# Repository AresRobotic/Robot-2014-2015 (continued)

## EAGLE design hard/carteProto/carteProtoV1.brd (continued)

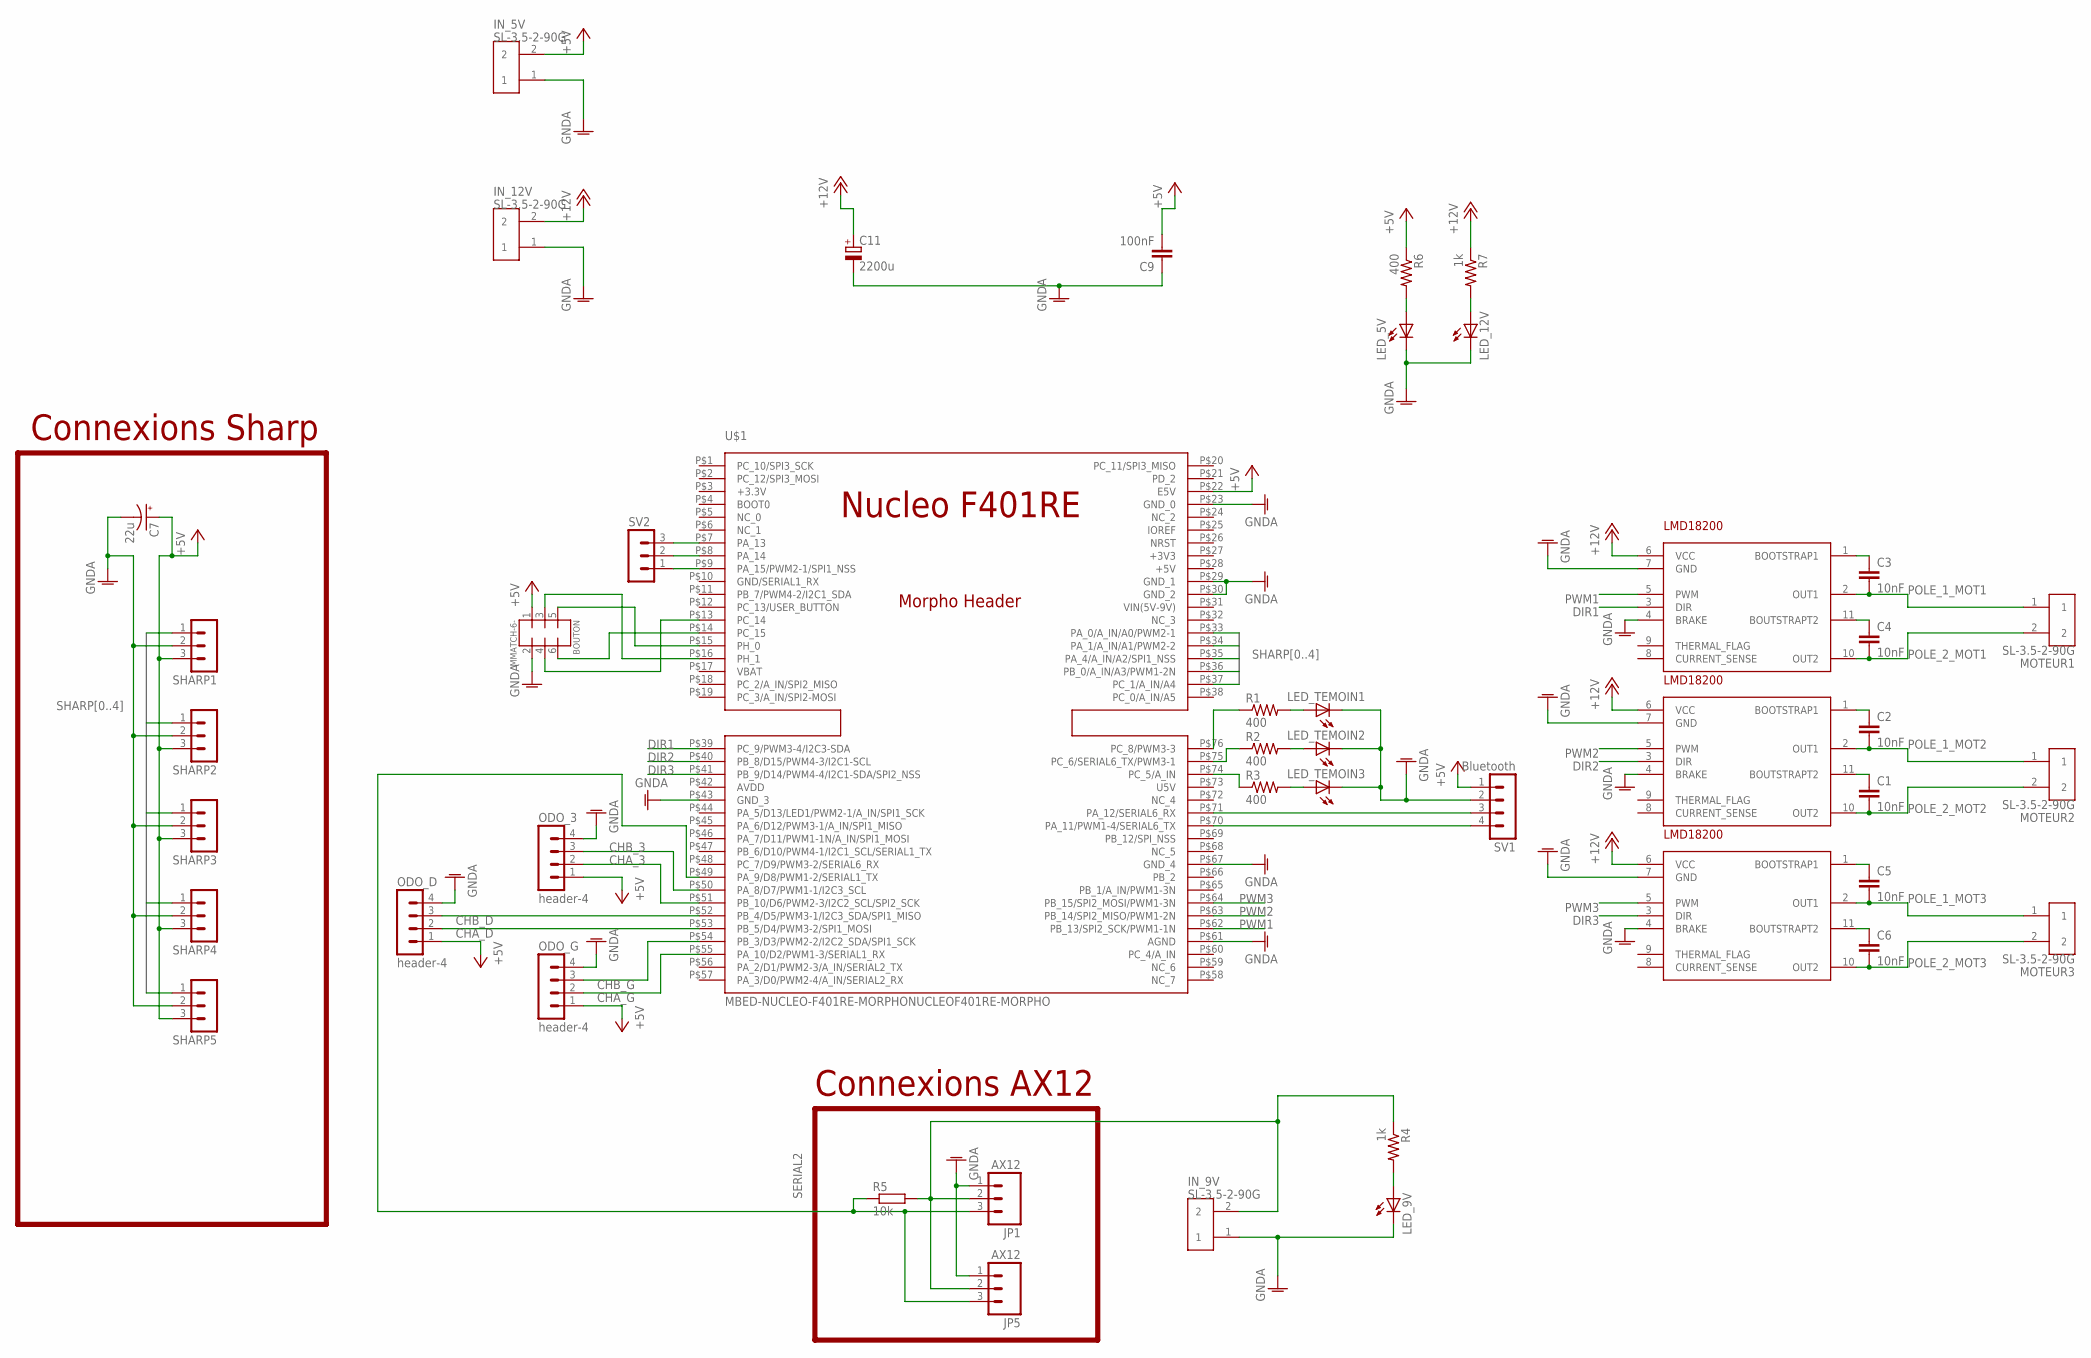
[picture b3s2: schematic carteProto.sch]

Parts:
BOUTON: MMATCH-6-; AMP-215079-6
C1, C2, C3, C4, C5, C6: 10nF; C0805
C7: 22u; CPOL-RADIAL-100UF-25V
C9: 100nF; C0805
C11: 2200u; TT5D11
IN_5V, IN_9V, IN_12V: SL-3.5-2-90G
JP1, JP5: AX12; MOLEX-1X3
LED_5V, LED_9V, LED_12V: LEDCHIPLED_0805; CHIPLED_0805
LED_TEMOIN1, LED_TEMOIN2, LED_TEMOIN3: LEDCHIPLED_0805; CHIPLED_0805
MOTEUR1, MOTEUR2, MOTEUR3: SL-3.5-2-90G
ODO_3: header-4; MA04-1
ODO_D: header-4; MA04-1
ODO_G: header-4; MA04-1
R1, R2, R3, R6: 400; 0805
R4, R7: 1k; 0805
R5: 10k; M0805
SHARP1, SHARP2, SHARP3, SHARP4, SHARP5: MA03-1
SV1: Bluetooth; MA04-1
SV2: MA03-1
U$1: MBED-NUCLEO-F401RE-MORPHONUCLEOF401RE-MORPHO; MORPHO-HEADERS
U$2, U$3, U$4: LMD18200

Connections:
+5V: BOUTON.1 (3), C7.1 (+), C9.2, IN_5V.2, ODO_3.1, ODO_D.1, ODO_G.1, R6.1, SHARP1.3, SHARP2.3, SHARP3.3, SHARP4.3, SHARP5.3, SV1.1, U$1.P$22 (E5V); also elsewhere on the board
CHA_3: ODO_3.2, U$1.P$51 (PB_10/D6/PWM2-3/I2C2_SCL/SPI2_SCK)
CHA_D: ODO_D.2, U$1.P$53 (PB_5/D4/PWM3-2/SPI1_MOSI)
CHA_G: ODO_G.2, U$1.P$55 (PA_10/D2/PWM1-3/SERIAL1_RX)
CHB_3: ODO_3.3, U$1.P$50 (PA_8/D7/PWM1-1/I2C3_SCL)
CHB_D: ODO_D.3, U$1.P$52 (PB_4/D5/PWM3-1/I2C3_SDA/SPI1_MISO)
CHB_G: ODO_G.3, U$1.P$54 (PB_3/D3/PWM2-2/I2C2_SDA/SPI1_SCK)
DIR1: U$1.P$39 (PC_9/PWM3-4/I2C3-SDA), U$2.3 (DIR)
DIR2: U$1.P$40 (PB_8/D15/PWM4-3/I2C1-SCL), U$3.3 (DIR)
DIR3: U$1.P$41 (PB_9/D14/PWM4-4/I2C1-SDA/SPI2_NSS), U$4.3 (DIR)
GNDA: BOUTON.2 (4), C7.2 (-), C9.1, C11.-, IN_5V.1, IN_9V.1, IN_12V.1, JP1.1, JP5.1, LED_5V.C, LED_9V.C, LED_12V.C, LED_TEMOIN1.C, LED_TEMOIN2.C, LED_TEMOIN3.C, ODO_3.4, ODO_D.4, ODO_G.4, SHARP1.2, SHARP2.2, SHARP3.2, SHARP4.2, SHARP5.2, SV1.2, U$1.P$23 (GND_0), U$1.P$29 (GND_1), U$1.P$30 (GND_2), U$1.P$43 (GND_3), U$1.P$61 (AGND), U$1.P$67 (GND_4), U$2.4 (BRAKE), U$2.7 (GND), U$3.4 (BRAKE), U$3.7 (GND), U$4.4 (BRAKE), U$4.7 (GND); also elsewhere on the board
unnamed: C1.1, U$3.11 (BOUTSTRAPT2)
unnamed: C5.1, U$4.1 (BOOTSTRAP1)
unnamed: C2.1, U$3.1 (BOOTSTRAP1)
unnamed: C6.1, U$4.11 (BOUTSTRAPT2)
unnamed: C3.1, U$2.1 (BOOTSTRAP1)
unnamed: SV1.3, U$1.P$71 (PA_12/SERIAL6_RX)
unnamed: C4.1, U$2.11 (BOUTSTRAPT2)
unnamed: SV1.4, U$1.P$70 (PA_11/PWM1-4/SERIAL6_TX)
unnamed: LED_5V.A, R6.2
unnamed: LED_TEMOIN3.A, R3.2
unnamed: LED_12V.A, R7.2
unnamed: R1.1, U$1.P$76 (PC_8/PWM3-3)
unnamed: R2.1, U$1.P$75 (PC_6/SERIAL6_TX/PWM3-1)
unnamed: R3.1, U$1.P$74 (PC_5/A_IN)
unnamed: LED_TEMOIN1.A, R1.2
unnamed: LED_TEMOIN2.A, R2.2
unnamed: BOUTON.3 (5), U$1.P$16 (PH_1)
unnamed: BOUTON.5 (7), U$1.P$15 (PH_0)
unnamed: BOUTON.6 (8), U$1.P$14 (PC_15)
unnamed: BOUTON.4 (6), U$1.P$13 (PC_14)
unnamed: SV2.3, U$1.P$7 (PA_13)
unnamed: SV2.2, U$1.P$8 (PA_14)
unnamed: SV2.1, U$1.P$9 (PA_15/PWM2-1/SPI1_NSS)
unnamed: LED_9V.A, R4.2
POLE_1_MOT1: C3.2, MOTEUR1.1, U$2.2 (OUT1)
POLE_1_MOT2: C2.2, MOTEUR2.1, U$3.2 (OUT1)
POLE_1_MOT3: C5.2, MOTEUR3.1, U$4.2 (OUT1)
POLE_2_MOT1: C4.2, MOTEUR1.2, U$2.10 (OUT2)
POLE_2_MOT2: C1.2, MOTEUR2.2, U$3.10 (OUT2)
POLE_2_MOT3: C6.2, MOTEUR3.2, U$4.10 (OUT2)
PWM1: U$1.P$62 (PB_13/SPI2_SCK/PWM1-1N), U$2.5 (PWM)
PWM2: U$1.P$63 (PB_14/SPI2_MISO/PWM1-2N), U$3.5 (PWM)
PWM3: U$1.P$64 (PB_15/SPI2_MOSI/PWM1-3N), U$4.5 (PWM)
SERIAL2: JP1.3, JP5.3, R5.1, U$1.P$49 (PA_9/D8/PWM1-2/SERIAL1_TX); also elsewhere on the board
SHARP0: SHARP1.1, U$1.P$33 (PA_0/A_IN/A0/PWM2-1)
SHARP1: SHARP2.1, U$1.P$34 (PA_1/A_IN/A1/PWM2-2)
SHARP2: SHARP3.1, U$1.P$35 (PA_4/A_IN/A2/SPI1_NSS)
SHARP3: SHARP4.1, U$1.P$36 (PB_0/A_IN/A3/PWM1-2N)
SHARP4: SHARP5.1, U$1.P$37 (PC_1/A_IN/A4)

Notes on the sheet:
Connexions Sharp
Connexions AX12

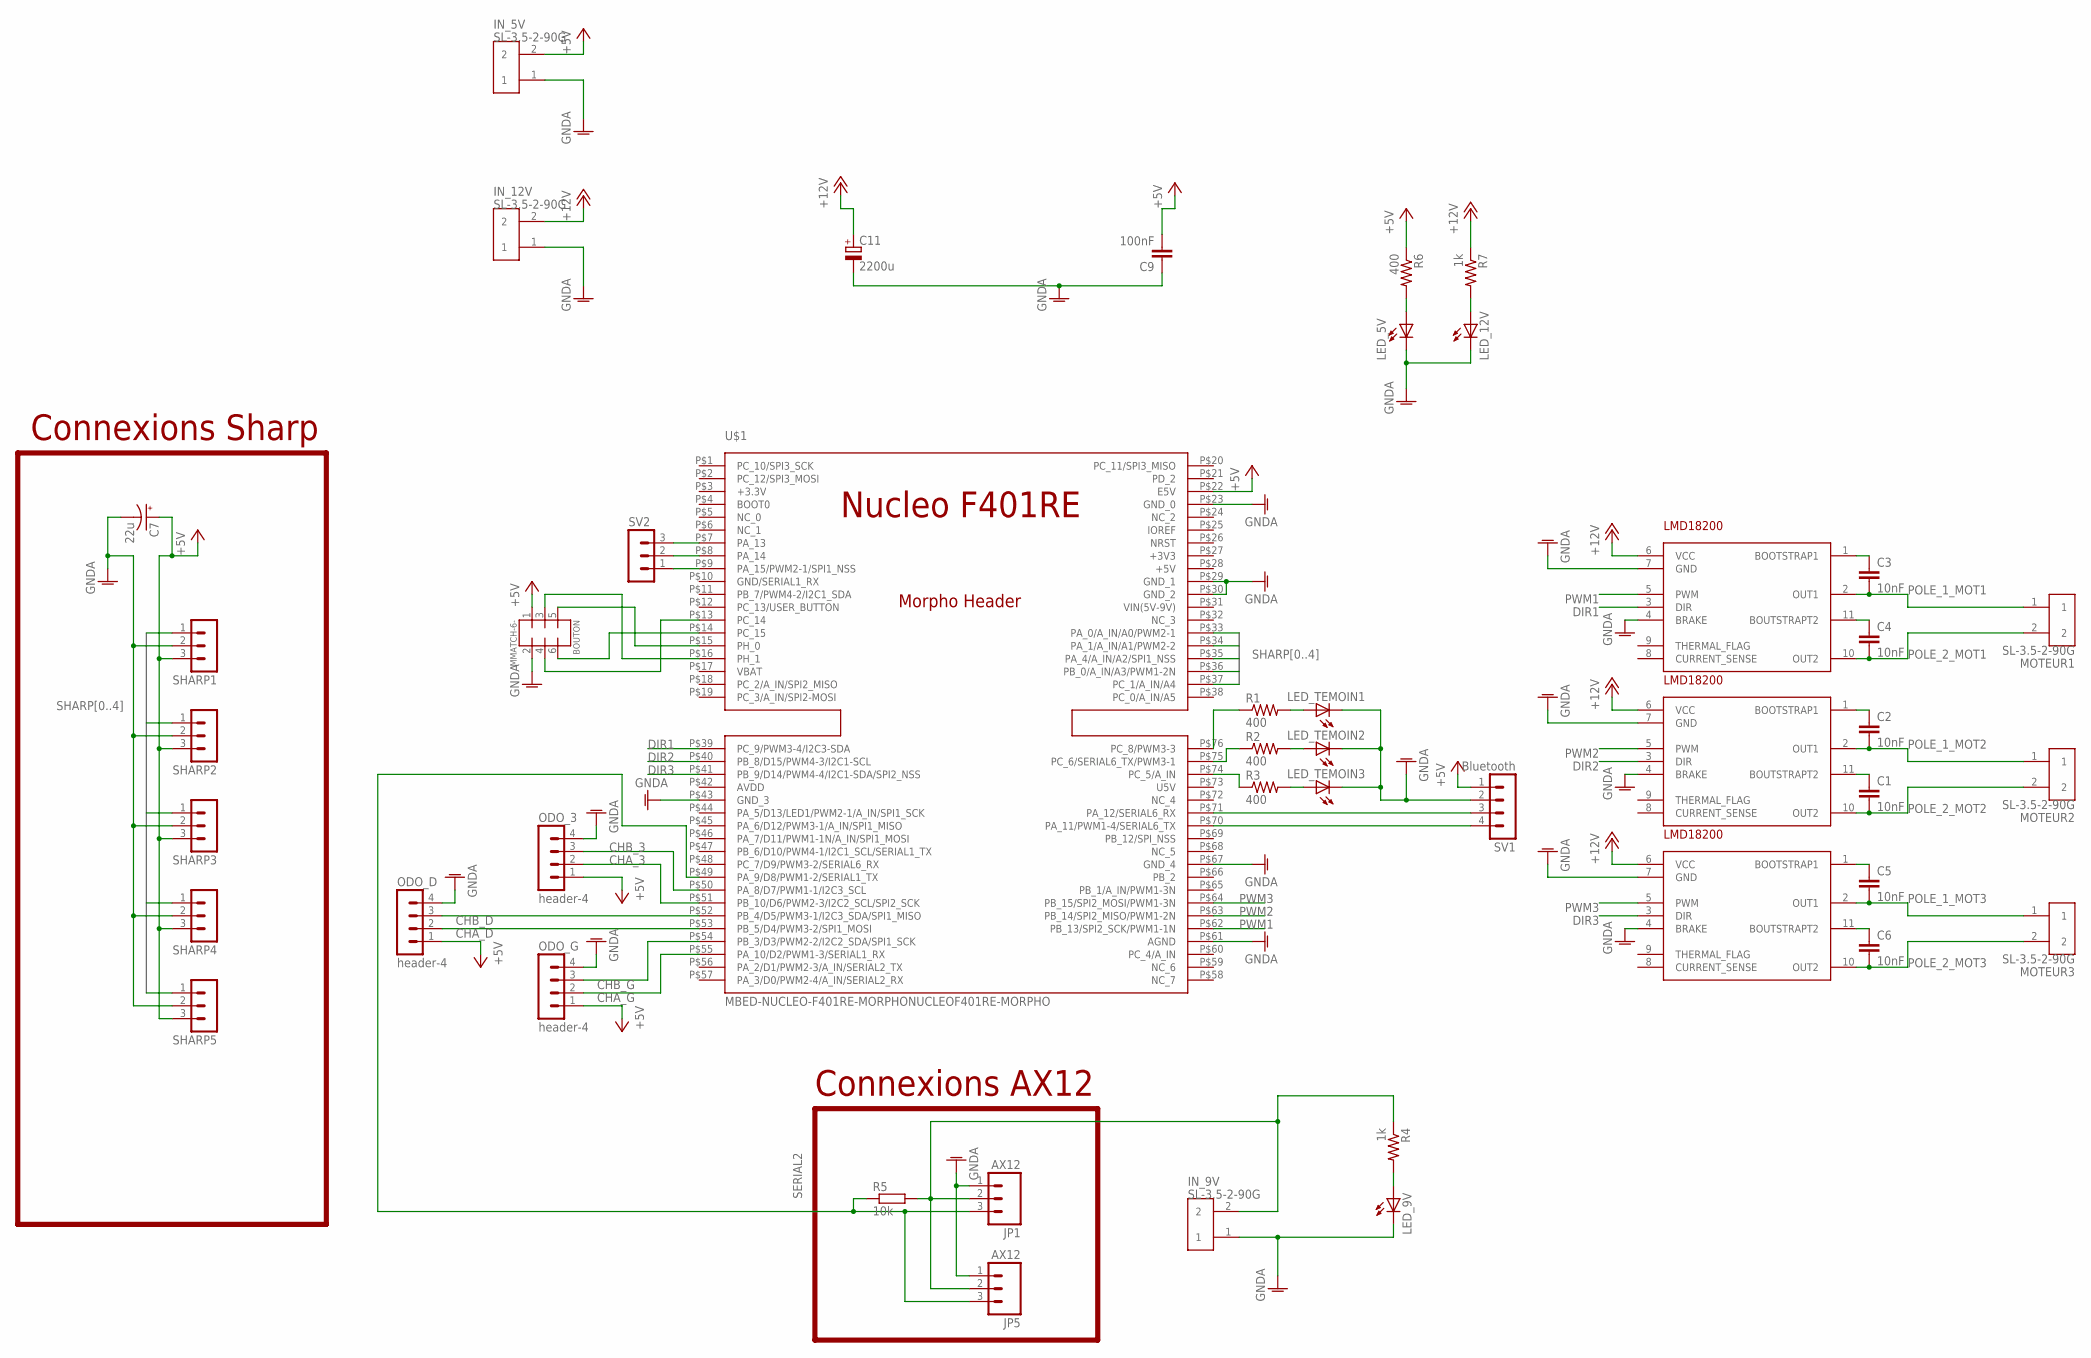
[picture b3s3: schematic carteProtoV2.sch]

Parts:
BOUTON: MMATCH-6-; AMP-215079-6
C1, C2, C3, C4, C5, C6: 10nF; C0805
C7: 22u; CPOL-RADIAL-100UF-25V
C9: 100nF; C0805
C11: 2200u; TT5D11
IN_5V, IN_9V, IN_12V: SL-3.5-2-90G
JP1, JP5: AX12; MOLEX-1X3
LED_5V, LED_9V, LED_12V: LEDCHIPLED_0805; CHIPLED_0805
LED_TEMOIN1, LED_TEMOIN2, LED_TEMOIN3: LEDCHIPLED_0805; CHIPLED_0805
MOTEUR1, MOTEUR2, MOTEUR3: SL-3.5-2-90G
ODO_3: header-4; MA04-1
ODO_D: header-4; MA04-1
ODO_G: header-4; MA04-1
R1, R2, R3, R6: 400; 0805
R4, R7: 1k; 0805
R5: 10k; M0805
SHARP1, SHARP2, SHARP3, SHARP4, SHARP5: MA03-1
SV1: Bluetooth; MA04-1
SV2: MA03-1
U$1: MBED-NUCLEO-F401RE-MORPHONUCLEOF401RE-MORPHO; MORPHO-HEADERS
U$2, U$3, U$4: LMD18200

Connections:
+5V: BOUTON.1 (3), C7.1 (+), C9.2, IN_5V.2, ODO_3.1, ODO_D.1, ODO_G.1, R6.1, SHARP1.3, SHARP2.3, SHARP3.3, SHARP4.3, SHARP5.3, SV1.1, U$1.P$22 (E5V); also elsewhere on the board
CHA_3: ODO_3.2, U$1.P$51 (PB_10/D6/PWM2-3/I2C2_SCL/SPI2_SCK)
CHA_D: ODO_D.2, U$1.P$53 (PB_5/D4/PWM3-2/SPI1_MOSI)
CHA_G: ODO_G.2, U$1.P$55 (PA_10/D2/PWM1-3/SERIAL1_RX)
CHB_3: ODO_3.3, U$1.P$50 (PA_8/D7/PWM1-1/I2C3_SCL)
CHB_D: ODO_D.3, U$1.P$52 (PB_4/D5/PWM3-1/I2C3_SDA/SPI1_MISO)
CHB_G: ODO_G.3, U$1.P$54 (PB_3/D3/PWM2-2/I2C2_SDA/SPI1_SCK)
DIR1: U$1.P$39 (PC_9/PWM3-4/I2C3-SDA), U$2.3 (DIR)
DIR2: U$1.P$40 (PB_8/D15/PWM4-3/I2C1-SCL), U$3.3 (DIR)
DIR3: U$1.P$41 (PB_9/D14/PWM4-4/I2C1-SDA/SPI2_NSS), U$4.3 (DIR)
GNDA: BOUTON.2 (4), C7.2 (-), C9.1, C11.-, IN_5V.1, IN_9V.1, IN_12V.1, JP1.1, JP5.1, LED_5V.C, LED_9V.C, LED_12V.C, LED_TEMOIN1.C, LED_TEMOIN2.C, LED_TEMOIN3.C, ODO_3.4, ODO_D.4, ODO_G.4, SHARP1.2, SHARP2.2, SHARP3.2, SHARP4.2, SHARP5.2, SV1.2, U$1.P$23 (GND_0), U$1.P$29 (GND_1), U$1.P$30 (GND_2), U$1.P$43 (GND_3), U$1.P$61 (AGND), U$1.P$67 (GND_4), U$2.4 (BRAKE), U$2.7 (GND), U$3.4 (BRAKE), U$3.7 (GND), U$4.4 (BRAKE), U$4.7 (GND); also elsewhere on the board
unnamed: C1.1, U$3.11 (BOUTSTRAPT2)
unnamed: C5.1, U$4.1 (BOOTSTRAP1)
unnamed: C2.1, U$3.1 (BOOTSTRAP1)
unnamed: C6.1, U$4.11 (BOUTSTRAPT2)
unnamed: C3.1, U$2.1 (BOOTSTRAP1)
unnamed: SV1.3, U$1.P$71 (PA_12/SERIAL6_RX)
unnamed: C4.1, U$2.11 (BOUTSTRAPT2)
unnamed: SV1.4, U$1.P$70 (PA_11/PWM1-4/SERIAL6_TX)
unnamed: LED_5V.A, R6.2
unnamed: LED_TEMOIN3.A, R3.2
unnamed: LED_12V.A, R7.2
unnamed: R1.1, U$1.P$76 (PC_8/PWM3-3)
unnamed: R2.1, U$1.P$75 (PC_6/SERIAL6_TX/PWM3-1)
unnamed: R3.1, U$1.P$74 (PC_5/A_IN)
unnamed: LED_TEMOIN1.A, R1.2
unnamed: LED_TEMOIN2.A, R2.2
unnamed: BOUTON.3 (5), U$1.P$16 (PH_1)
unnamed: BOUTON.5 (7), U$1.P$15 (PH_0)
unnamed: BOUTON.6 (8), U$1.P$14 (PC_15)
unnamed: BOUTON.4 (6), U$1.P$13 (PC_14)
unnamed: SV2.3, U$1.P$7 (PA_13)
unnamed: SV2.2, U$1.P$8 (PA_14)
unnamed: SV2.1, U$1.P$9 (PA_15/PWM2-1/SPI1_NSS)
unnamed: LED_9V.A, R4.2
POLE_1_MOT1: C3.2, MOTEUR1.1, U$2.2 (OUT1)
POLE_1_MOT2: C2.2, MOTEUR2.1, U$3.2 (OUT1)
POLE_1_MOT3: C5.2, MOTEUR3.1, U$4.2 (OUT1)
POLE_2_MOT1: C4.2, MOTEUR1.2, U$2.10 (OUT2)
POLE_2_MOT2: C1.2, MOTEUR2.2, U$3.10 (OUT2)
POLE_2_MOT3: C6.2, MOTEUR3.2, U$4.10 (OUT2)
PWM1: U$1.P$62 (PB_13/SPI2_SCK/PWM1-1N), U$2.5 (PWM)
PWM2: U$1.P$63 (PB_14/SPI2_MISO/PWM1-2N), U$3.5 (PWM)
PWM3: U$1.P$64 (PB_15/SPI2_MOSI/PWM1-3N), U$4.5 (PWM)
SERIAL2: JP1.3, JP5.3, R5.1, U$1.P$49 (PA_9/D8/PWM1-2/SERIAL1_TX); also elsewhere on the board
SHARP0: SHARP1.1, U$1.P$33 (PA_0/A_IN/A0/PWM2-1)
SHARP1: SHARP2.1, U$1.P$34 (PA_1/A_IN/A1/PWM2-2)
SHARP2: SHARP3.1, U$1.P$35 (PA_4/A_IN/A2/SPI1_NSS)
SHARP3: SHARP4.1, U$1.P$36 (PB_0/A_IN/A3/PWM1-2N)
SHARP4: SHARP5.1, U$1.P$37 (PC_1/A_IN/A4)

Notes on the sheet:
Connexions Sharp
Connexions AX12

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
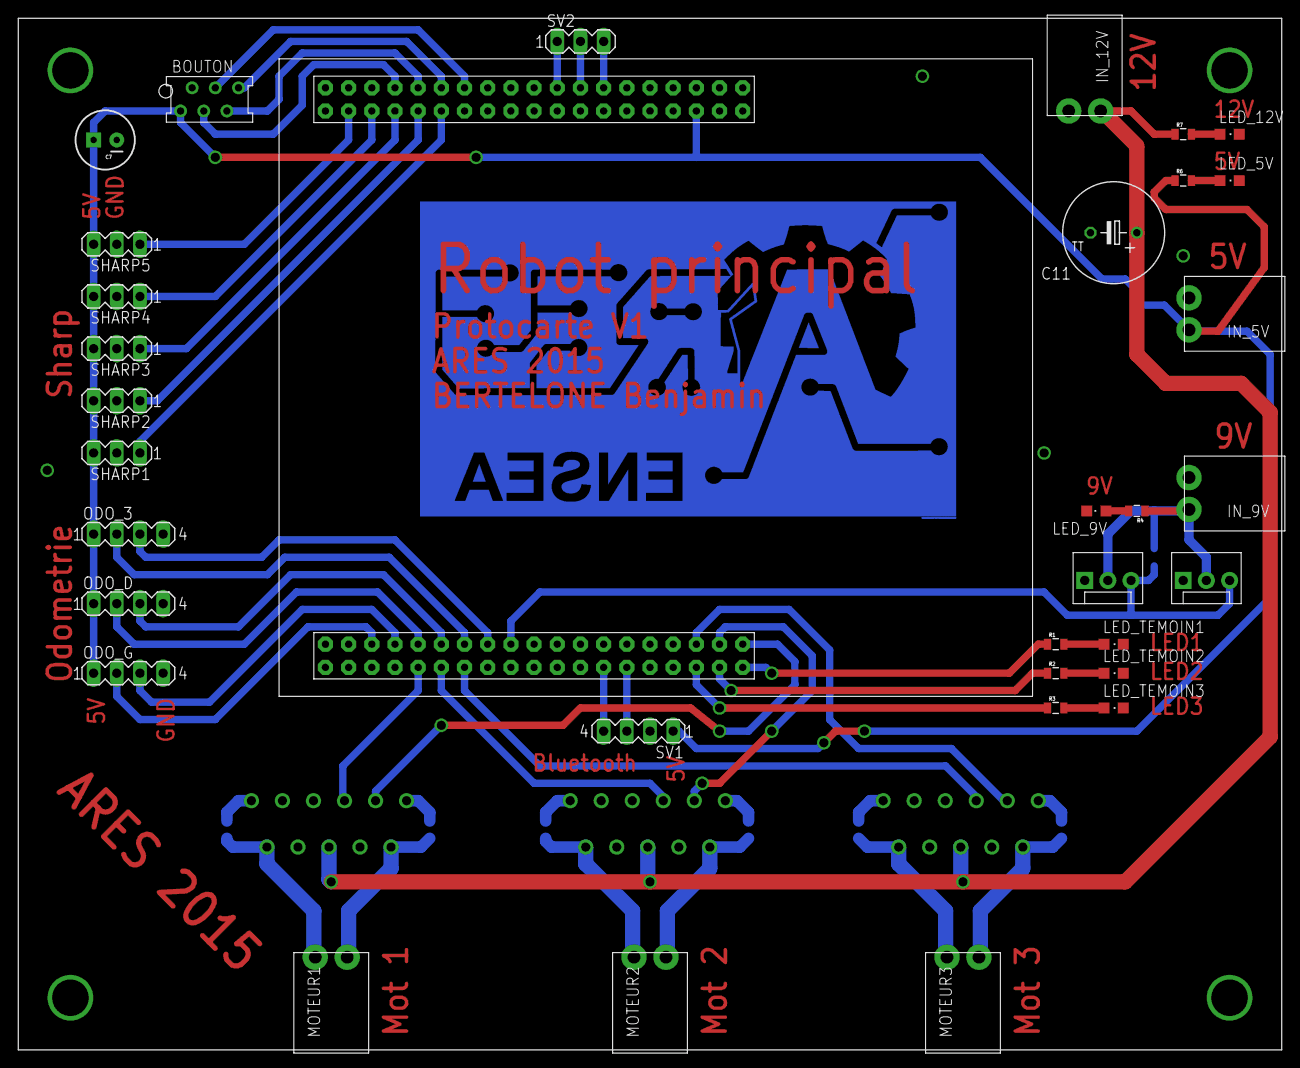
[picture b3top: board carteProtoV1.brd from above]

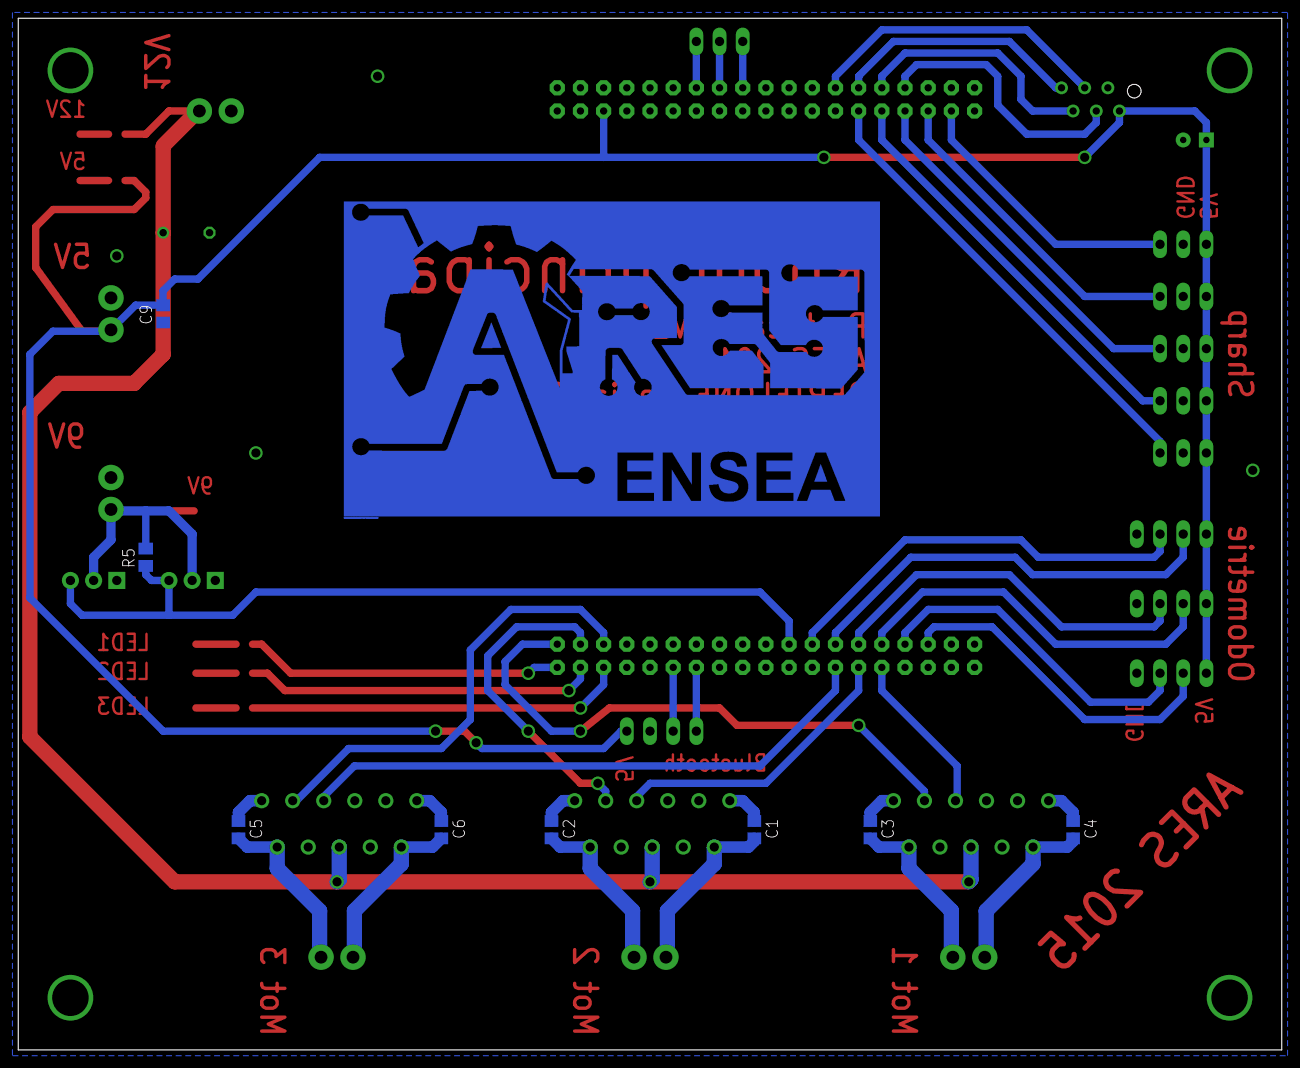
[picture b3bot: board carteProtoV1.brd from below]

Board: 2 copper layers, 138.4 x 113.0 mm, 45 parts (8 on the bottom side), 52 nets.

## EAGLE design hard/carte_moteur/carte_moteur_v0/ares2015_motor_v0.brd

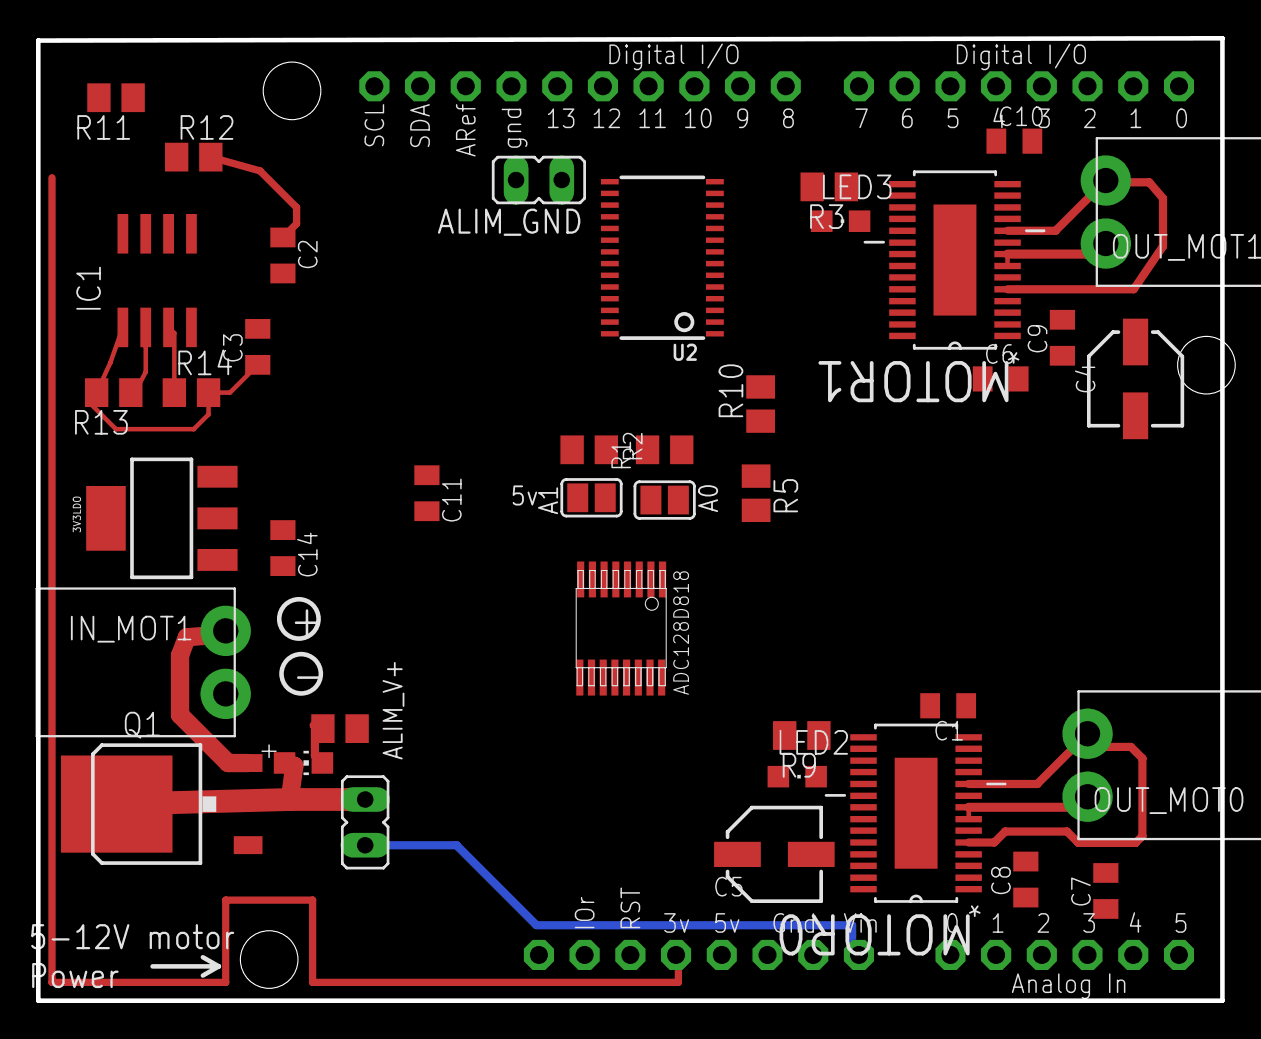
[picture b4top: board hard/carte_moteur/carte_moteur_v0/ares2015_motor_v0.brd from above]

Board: 2 copper layers, 65.8 x 53.5 mm, 41 parts (0 on the bottom side), 36 nets.

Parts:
3V3LDO: SOT223
A0, A1: SJ
ALIM_GND: JP1
ALIM_V+: JP1
C1, C10: 0.47uF; C0805K
C2, C3, C8, C9, C11, C14: 0.1uF; C0805K
C4, C5: 22uF/16v; PANASONIC_C
C6, C7: 0.01uF; C0805K
IC1: ISO1541; SO-08
IN_MOT1: SL-3.5-2-90G
LED1: Green; CHIP-LED0805
LED2, LED3: rouge; CHIPLED_0805
MOTOR0, MOTOR1: DRV8828PWP; SOP65P640X120-29N
OUT_MOT0, OUT_MOT1: SL-3.5-2-90G
Q1: AOD417; D-PAK_TO252AA
R1, R2: 10k; M0805
R3, R9: 330; M0805
R4: 1K; M0805
R5, R10: 0.25; M0805
R11, R12, R13, R14: 1.5k; M0805
U1: ARDUINOR3-BPLACE
U2: PCA9685; TSSOP28
U$6: LMD128D818; ADC128D818

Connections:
+12V: 3V3LDO.3, ALIM_V+.1, C4.+, C5.+, C8.2, C9.2, LED1.A, MOTOR0.4, MOTOR0.11, MOTOR1.4, MOTOR1.11, Q1.4
A0: A0.2, R1.2, U2.1, U$6.7
A1: A1.2, R2.2, U2.2, U$6.8
ADC0: MOTOR0.6, MOTOR0.9, R10.1, U$6.16
ADC1: MOTOR1.6, MOTOR1.9, R5.1, U$6.15
GND: 3V3LDO.1, ALIM_GND.1, C1.2, C3.2, C4.-, C5.-, C10.2, C11.2, C14.2, IC1.4, IN_MOT1.1, MOTOR0.14, MOTOR0.28, MOTOR0.29, MOTOR1.14, MOTOR1.28, MOTOR1.29, Q1.1, R1.1, R2.1, R4.1, R5.2, R10.2, U2.14, U2.23, U2.25, U$6.4
GND_CLEAN: ALIM_GND.2, C2.2, IC1.5, U1.GND
unnamed: C6.1, MOTOR1.1
unnamed: MOTOR0.7, MOTOR0.8, OUT_MOT0.2
unnamed: C6.2, MOTOR1.2
unnamed: C9.1, MOTOR1.3
unnamed: MOTOR0.5, MOTOR0.10, OUT_MOT0.1
unnamed: LED3.C, MOTOR1.18
unnamed: LED3.A, R3.2
unnamed: MOTOR1.5, MOTOR1.10, OUT_MOT1.1
unnamed: MOTOR1.7, MOTOR1.8, OUT_MOT1.2
unnamed: C7.1, MOTOR0.1
unnamed: C7.2, MOTOR0.2
unnamed: C8.1, MOTOR0.3
unnamed: LED2.A, R9.2
unnamed: LED2.C, MOTOR0.18
unnamed: LED1.C, R4.2
unnamed: IN_MOT1.2, Q1.3
PWM0: MOTOR0.21, U2.6
PWM1: MOTOR0.20, U2.7
PWM2: MOTOR1.21, U2.8
PWM3: MOTOR1.20, U2.9
SCL: IC1.3, R14.1, U2.26, U$6.3
SCL_CLEAN: IC1.6, R11.1, U1.SCL
SDA: IC1.2, R13.1, U2.27, U$6.2
SDA_CLEAN: IC1.7, R12.1, U1.SDA
V3POUT0: C1.1, MOTOR0.12, MOTOR0.13, MOTOR0.15
V3POUT1: C10.1, MOTOR1.12, MOTOR1.13, MOTOR1.15
VCC: 3V3LDO.2, 3V3LDO.4, A0.1, A1.1, C3.1, C11.1, C14.1, IC1.1, MOTOR0.16, MOTOR0.17, MOTOR0.19, MOTOR0.23, MOTOR0.24, MOTOR0.25, MOTOR0.26, MOTOR0.27, MOTOR1.16, MOTOR1.17, MOTOR1.19, MOTOR1.23, MOTOR1.24, MOTOR1.25, MOTOR1.26, MOTOR1.27, R3.1, R9.1, R13.2, R14.2, U2.24, U2.28, U$6.5
VCC_CLEAN: C2.1, IC1.8, R11.2, R12.2, U1.3V
VIN_ARDUINO: ALIM_V+.2, U1.VIN

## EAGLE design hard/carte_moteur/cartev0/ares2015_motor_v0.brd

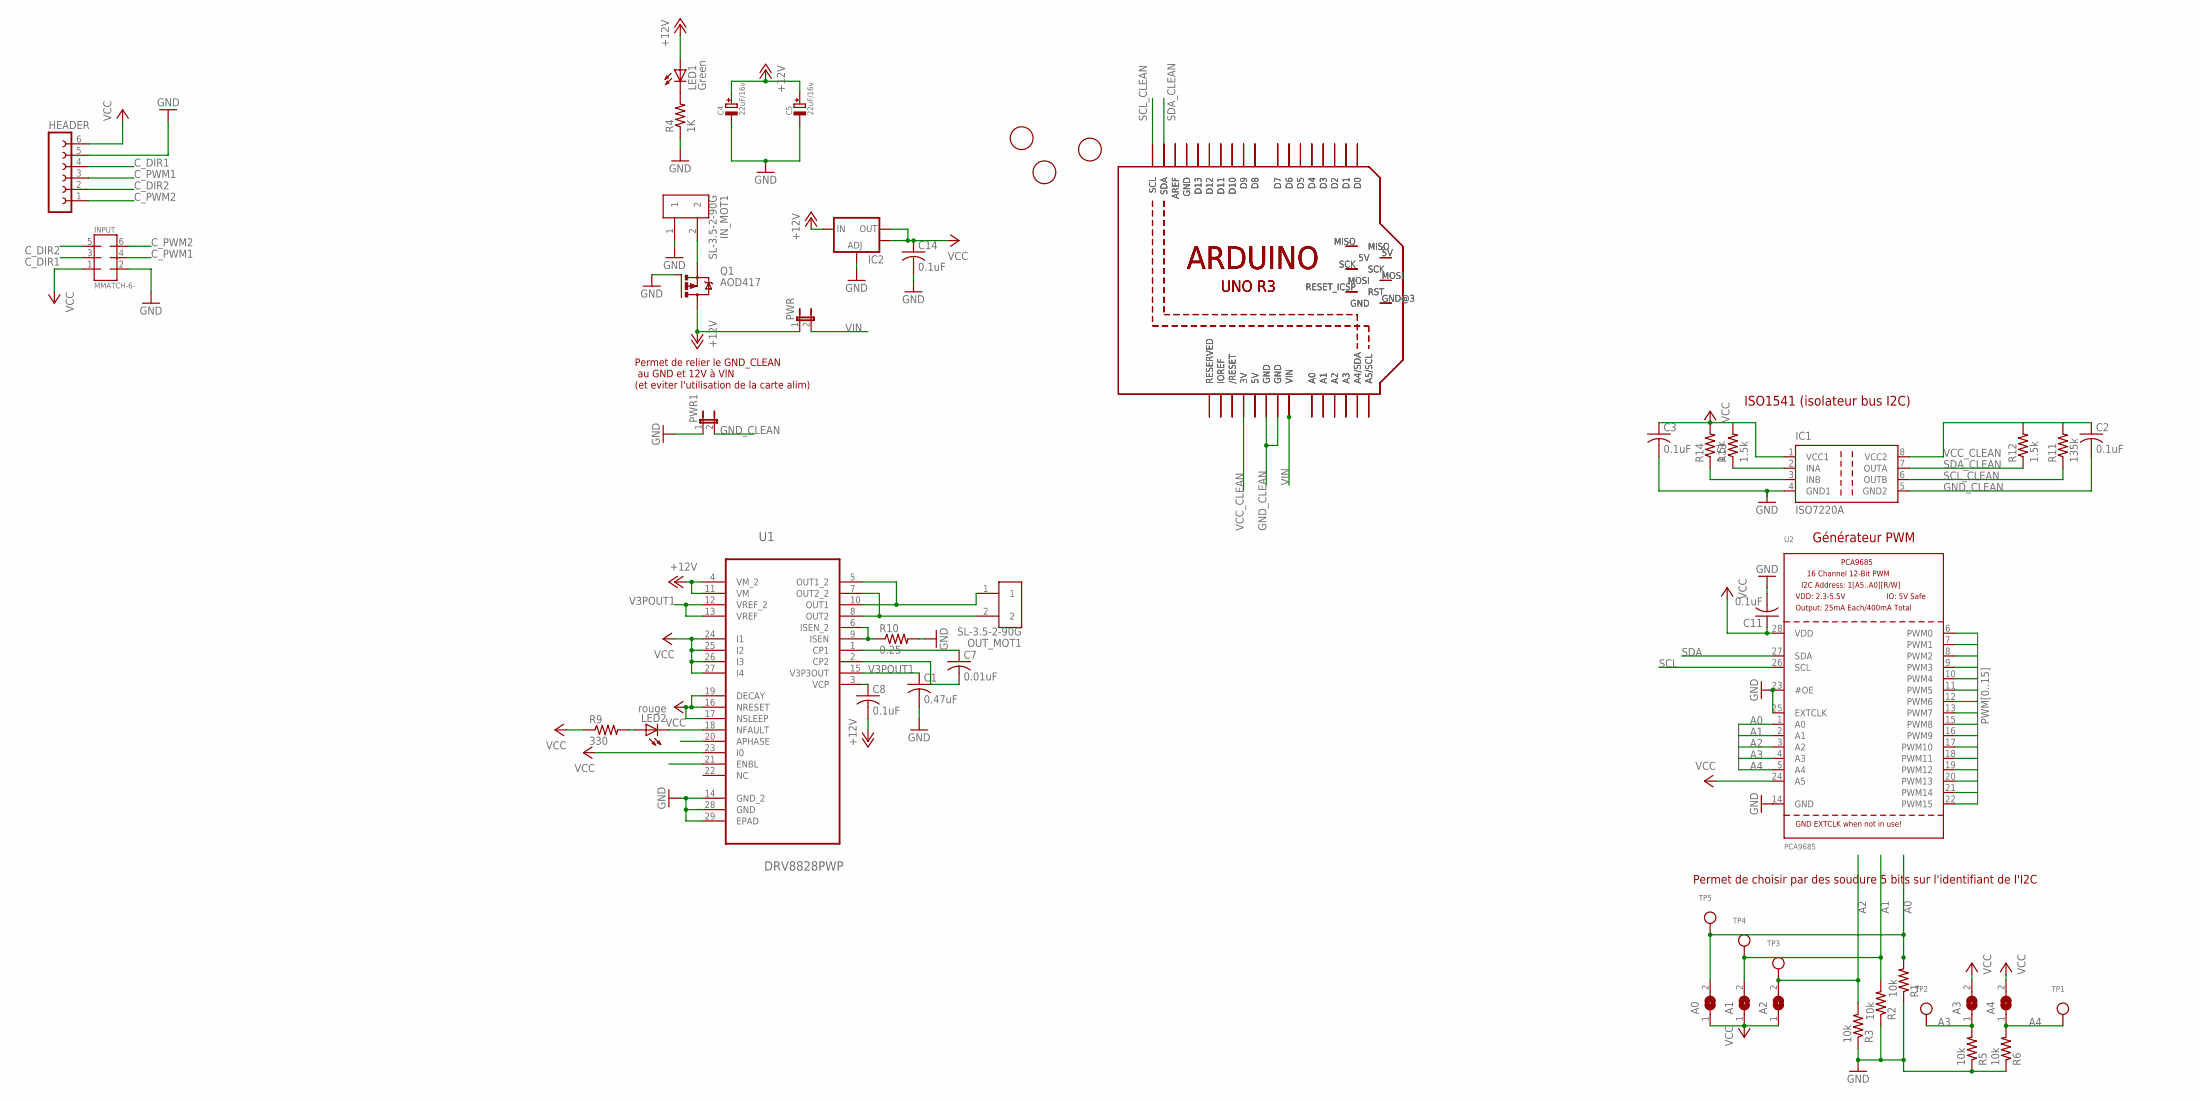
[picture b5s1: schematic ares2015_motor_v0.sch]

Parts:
A0, A1, A2, A3, A4: SJ
C1: 0.47uF; C0805K
C2, C3, C8, C11, C14: 0.1uF; C0805K
C4, C5: 22uF/16v; PANASONIC_C
C7: 0.01uF; C0805K
HEADER: FE06-1; FE06
IC1: ISO7220A; SO-08
IC2: V_REG_LM1117SOT223; SOT223
INPUT: MMATCH-6-; AMP-215079-6
IN_MOT1: SL-3.5-2-90G
LED1: Green; CHIP-LED0805
LED2: rouge; CHIPLED_0805
OUT_MOT1: SL-3.5-2-90G
PWR, PWR1: JP1E; JP1
Q1: AOD417; D-PAK_TO252AA
R1, R2, R3, R5, R6: 10k; R0805
R4: 1K; R0805
R9: 330; R0805
R10: 0.25; R0805
R11: 135k; R0805
R12, R13, R14: 1.5k; R0805
TP1, TP2, TP3, TP4, TP5: TESTPOINTROUND2MM; TESTPOINT_ROUND_2MM
U1: DRV8828PWP; SOP65P640X120-29N
U2: PCA9685; TSSOP28
U$1, U$5: ARDUINO_R3_ICSP; ARDUINOR3_ICSP
U$2, U$3, U$4: FIDUCIAL; FIDUCIAL_1MM

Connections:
+12V: C4.+, C5.+, C8.2, IC2.3 (IN), LED1.A, PWR.1, Q1.4 (D), U1.4 (VM_2), U1.11 (VM)
/RST: U$1.RESET (/RESET), U$5.RESET (/RESET)
A0: A0.2, R1.2, TP5.P$1, U2.1 (A0)
A1: A1.2, R2.2, TP4.P$1, U2.2 (A1)
A2: A2.2, R3.2, TP3.P$1, U2.3 (A2)
A3: A3.1, R5.2, TP2.P$1, U2.4 (A3)
A4: A4.1, R6.2, TP1.P$1, U2.5 (A4)
C_DIR1: HEADER.4, INPUT.3 (5)
C_DIR2: HEADER.2, INPUT.5 (7)
C_PWM1: HEADER.3, INPUT.4 (6)
C_PWM2: HEADER.1, INPUT.6 (8)
GND: C1.2, C3.2, C4.-, C5.-, C11.2, C14.2, HEADER.5, IC1.4 (GND1), IC2.1 (ADJ), INPUT.2 (4), IN_MOT1.1, PWR1.1, Q1.1 (G), R1.1, R2.1, R3.1, R4.1, R5.1, R6.1, R10.2, U1.14 (GND_2), U1.28 (GND), U1.29 (EPAD), U2.14 (GND), U2.23 (#OE), U2.25 (EXTCLK)
GND_CLEAN: C2.2, IC1.5 (GND2), PWR1.2, U$1.GND@1 (GND), U$1.GND@2 (GND), U$5.GND@1 (GND), U$5.GND@2 (GND)
unnamed: U$1.IOREF, U$5.IOREF
unnamed: U$1.RESERVED, U$5.RESERVED
unnamed: U$1.MISO, U$5.MISO
unnamed: U$1.D9, U$5.D9
unnamed: U$1.5V, U$5.5V
unnamed: U$1.MOSI, U$5.MOSI
unnamed: U$1.5V_ICSP (5V), U$5.5V_ICSP (5V)
unnamed: U$1.GND@3 (GND), U$5.GND@3 (GND)
unnamed: U$1.SCK, U$5.SCK
unnamed: OUT_MOT1.2, U1.7 (OUT2_2), U1.8 (OUT2)
unnamed: U$1.RESET_ICSP (RST), U$5.RESET_ICSP (RST)
unnamed: OUT_MOT1.1, U1.5 (OUT1_2), U1.10 (OUT1)
unnamed: U$1.A5 (A5/SCL), U$5.A5 (A5/SCL)
unnamed: U$1.A4 (A4/SDA), U$5.A4 (A4/SDA)
unnamed: IC1.2 (INA), R13.1
unnamed: IC1.3 (INB), R14.1
unnamed: U$1.A0, U$5.A0
unnamed: U$1.A1, U$5.A1
unnamed: U$1.A2, U$5.A2
unnamed: U$1.A3, U$5.A3
unnamed: U$1.D0, U$5.D0
unnamed: U$1.D1, U$5.D1
unnamed: U$1.D2, U$5.D2
unnamed: U$1.D4, U$5.D4
unnamed: U$1.D7, U$5.D7
unnamed: U$1.D8, U$5.D8
unnamed: U$1.D12, U$5.D12
unnamed: U$1.D13, U$5.D13
unnamed: U$1.AREF, U$5.AREF
unnamed: U$1.GND, U$5.GND
unnamed: R10.1, U1.6 (ISEN_2), U1.9 (ISEN)
unnamed: C7.1, U1.1 (CP1)
unnamed: C7.2, U1.2 (CP2)
unnamed: C8.1, U1.3 (VCP)
unnamed: LED2.A, R9.2
unnamed: LED2.C, U1.18 (NFAULT)
unnamed: LED1.C, R4.2
unnamed: IN_MOT1.2, Q1.3 (S)
PWM0: U2.6 (PWM0)
PWM0A: U$1.D6, U$5.D6
PWM0B: U$1.D5, U$5.D5
PWM1: U2.7 (PWM1)
PWM1B: U$1.D10, U$5.D10
PWM2: U2.8 (PWM2)
PWM2A: U$1.D11, U$5.D11
PWM2B: U$1.D3, U$5.D3
PWM3: U2.9 (PWM3)
PWM4: U2.10 (PWM4)
PWM5: U2.11 (PWM5)
PWM6: U2.12 (PWM6)
PWM7: U2.13 (PWM7)
PWM8: U2.15 (PWM8)
PWM9: U2.16 (PWM9)
PWM10: U2.17 (PWM10)
PWM11: U2.18 (PWM11)
PWM12: U2.19 (PWM12)
PWM13: U2.20 (PWM13)
PWM14: U2.21 (PWM14)
PWM15: U2.22 (PWM15)
SCL: U2.26 (SCL)
SCL_CLEAN: IC1.6 (OUTB), R11.1, U$1.SCL, U$5.SCL
SDA: U2.27 (SDA)
SDA_CLEAN: IC1.7 (OUTA), R12.1, U$1.SDA, U$5.SDA
V3POUT1: C1.1, U1.12 (VREF_2), U1.13 (VREF), U1.15 (V3P3OUT)
VCC: A0.1, A1.1, A2.1, A3.2, A4.2, C3.1, C11.1, C14.1, HEADER.6, IC1.1 (VCC1), IC2.2 (OUT), IC2.4 (OUT), INPUT.1 (3), R9.1, U1.16 (NRESET), U1.17 (NSLEEP), U1.19 (DECAY), U1.23 (I0), U1.24 (I1), U1.25 (I2), U1.26 (I3), U1.27 (I4), U2.24 (A5), U2.28 (VDD)
VCC_CLEAN: C2.1, IC1.8 (VCC2), R11.2, R12.2, U$1.3V, U$5.3V
VIN: PWR.2, U$1.VIN, U$5.VIN

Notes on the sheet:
ISO1541 (isolateur bus I2C)
Générateur PWM
Permet de choisir par des soudure 5 bits sur l'identifiant de l'I2C
Permet de relier le GND_CLEAN au GND et 12V à VIN (et eviter l'utilisation de la carte alim)

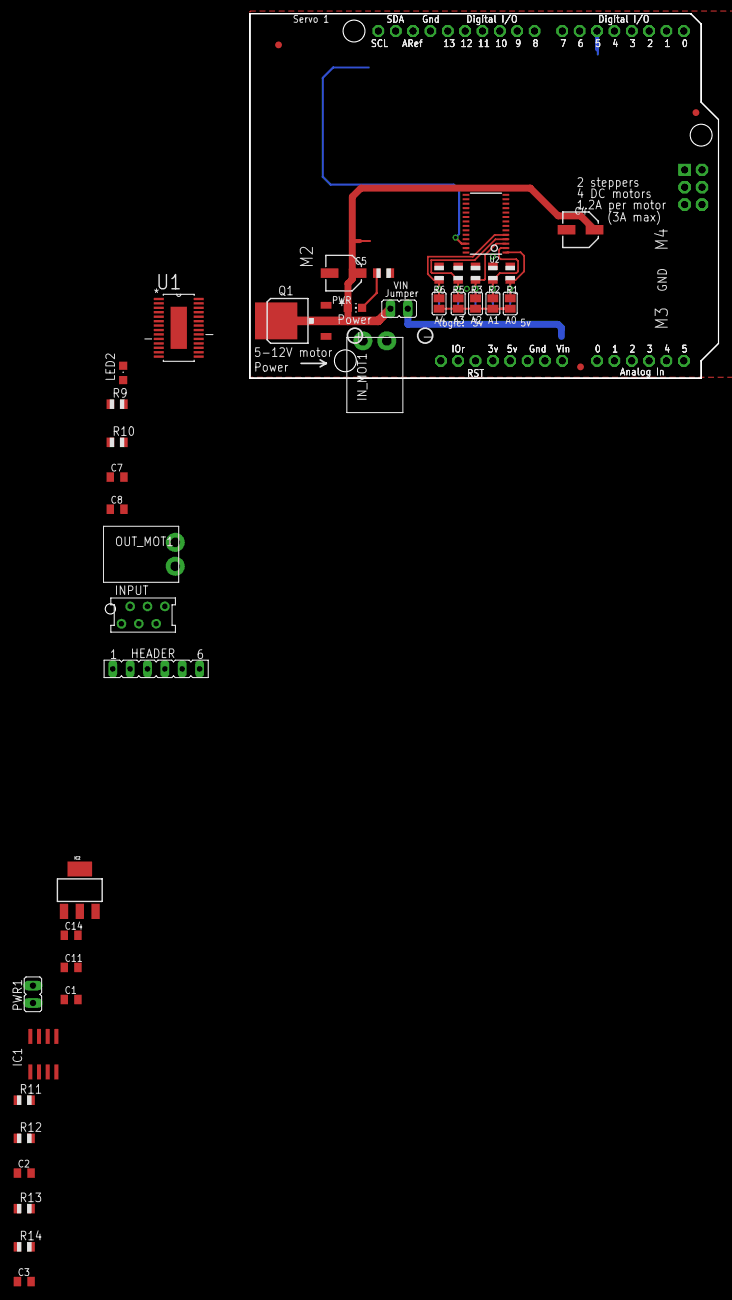
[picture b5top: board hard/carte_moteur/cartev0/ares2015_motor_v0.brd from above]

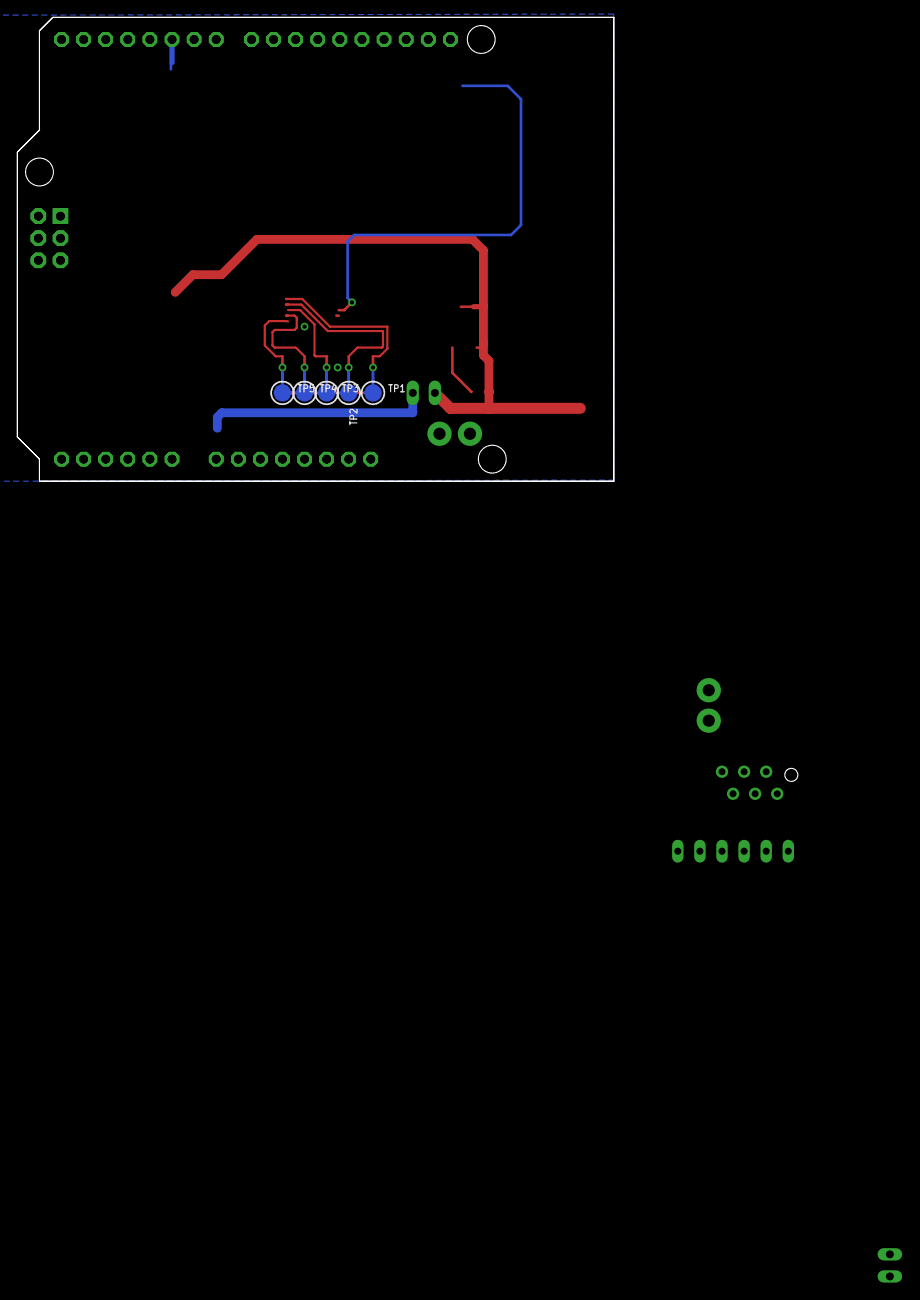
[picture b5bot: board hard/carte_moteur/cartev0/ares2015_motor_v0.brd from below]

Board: 2 copper layers, 68.6 x 53.3 mm, 49 parts (5 on the bottom side), 62 nets.
